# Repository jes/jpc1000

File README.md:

# JPC-1000

This is a repo containing Arduino code, KiCad files for PCBs, and FreeCAD files for the 3d-printed case.

Read more about the project on my blog: https://incoherency.co.uk/blog/stories/process-controller.html

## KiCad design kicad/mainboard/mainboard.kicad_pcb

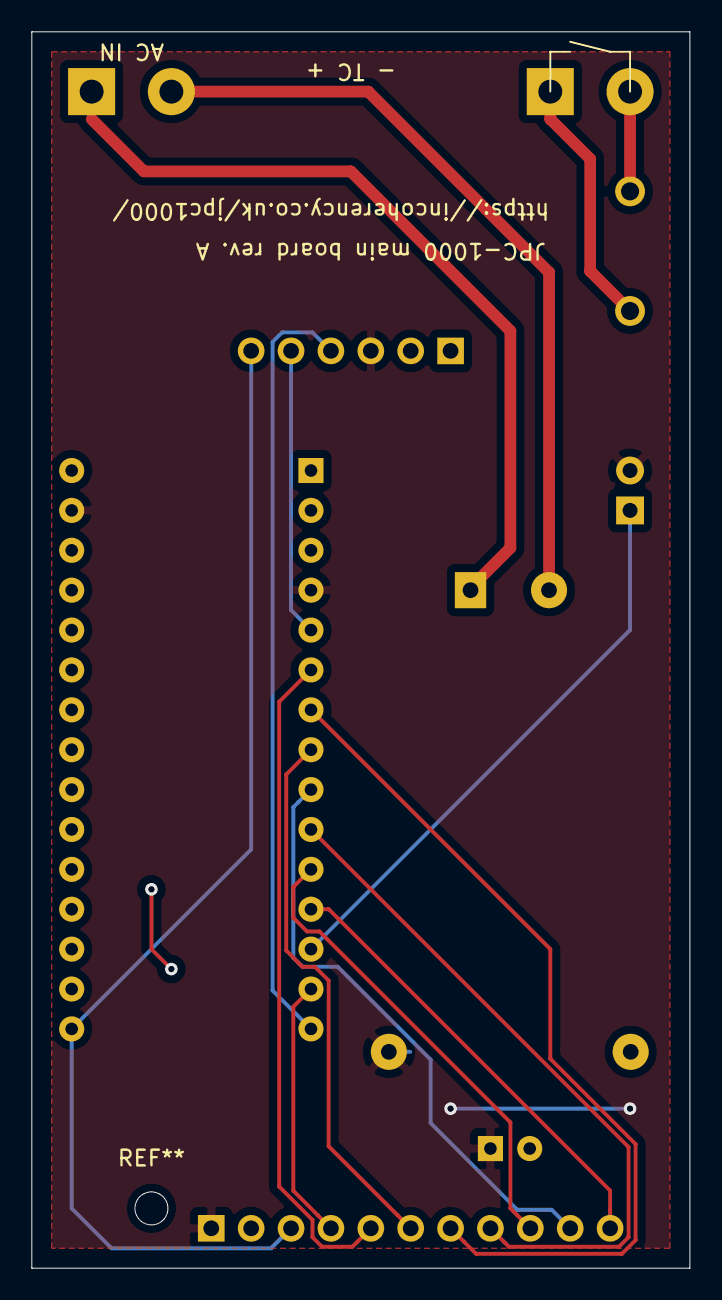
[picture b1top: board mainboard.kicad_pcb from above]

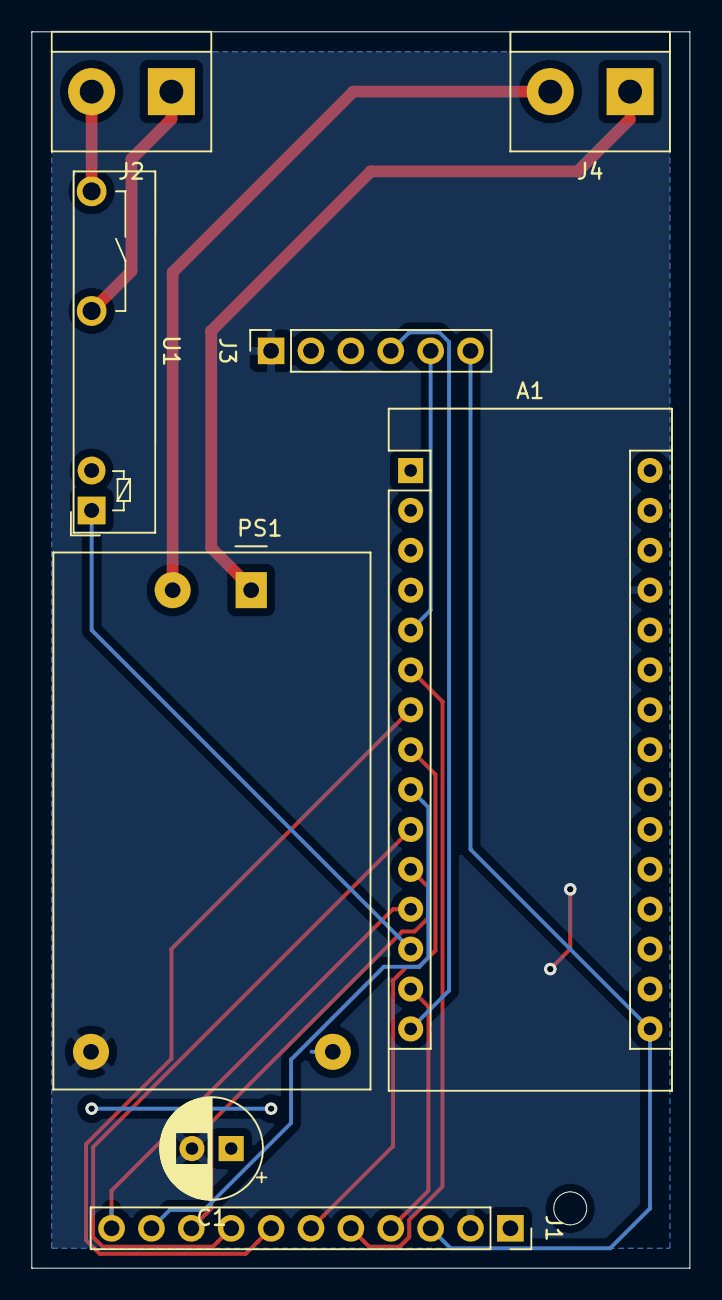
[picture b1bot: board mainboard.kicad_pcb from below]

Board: 2 copper layers, 41.9 x 78.7 mm, 8 parts (8 on the bottom side), 18 nets.

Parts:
A1: Arduino_Nano_v2.x; Arduino_Nano
C1: CP; CP_Radial_D6.3mm_P2.50mm
J1: Conn_01x11_Female; PinSocket_1x11_P2.54mm_Vertical
J2, J4: Screw_Terminal_01x02; TerminalBlock_bornier-2_P5.08mm
J3: Conn_01x06_Female; PinSocket_1x06_P2.54mm_Vertical
PS1: HLK-PM01; Converter_ACDC_HiLink_HLK-PMxx
U1: 34.81-8240; Omron-G3MB-202P

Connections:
unnamed: A1.5, J3.5
unnamed: A1.6, J1.5
unnamed: A1.7, J1.7
unnamed: A1.8, J1.6
unnamed: A1.9, J1.10
unnamed: A1.10, J1.8
unnamed: A1.11, J1.9
unnamed: A1.12, J1.11
unnamed: A1.13, U1.A2
unnamed: A1.14, J1.4
unnamed: A1.15, J3.4
unnamed: A1.16, J1.3, J3.6
unnamed: A1.27, C1.2, J1.2, J3.1, PS1.4
unnamed: A1.4, A1.29, C1.1, J1.1, J3.3, PS1.3, U1.A1
unnamed: J2.1, U1.11
unnamed: J2.2, U1.14
unnamed: J4.1, PS1.1
unnamed: J4.2, PS1.2

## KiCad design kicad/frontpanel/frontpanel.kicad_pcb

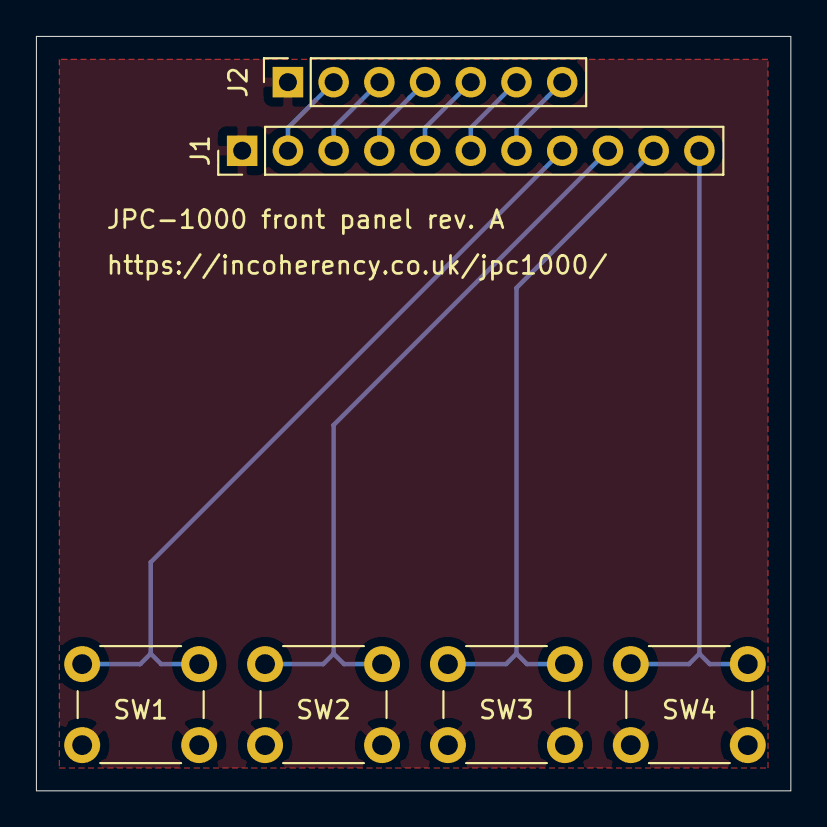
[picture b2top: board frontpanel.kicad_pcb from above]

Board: 2 copper layers, 41.9 x 41.9 mm, 6 parts (0 on the bottom side), 11 nets.

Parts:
J1: Conn_01x11_Male; PinHeader_1x11_P2.54mm_Vertical
J2: Conn_01x07_Female; PinSocket_1x07_P2.54mm_Vertical
SW1, SW2, SW3, SW4: SW_Push; SW_PUSH_6mm_H4.3mm

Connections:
unnamed: J1.1, J2.1, SW1.2, SW2.2, SW3.2, SW4.2
unnamed: J1.2, J2.2
unnamed: J1.3, J2.3
unnamed: J1.4, J2.4
unnamed: J1.5, J2.5
unnamed: J1.6, J2.6
unnamed: J1.7, J2.7
unnamed: J1.8, SW1.1
unnamed: J1.9, SW2.1
unnamed: J1.10, SW3.1
unnamed: J1.11, SW4.1

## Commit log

2019-08-17 Some segment editing ui
2019-08-18 Load/save config in EEPROM
2019-08-18 Draw segment descriptions (apart from duration because we can't format times yet)
2019-08-18 Add 'reset all' option, and switch heater on and off with duty cycle
2019-08-18 Format floats and times, add 'Save' button to segment editing menu
2019-08-18 Format times better, store min_time, use fewer segments because low on memory
2019-08-18 Free up 1% extra memory
2019-08-18 Store manual_control in eeprom; edit in menu
2019-08-18 Initial implementation of number editing
2019-08-18 Edit setpoint
2019-08-18 Key repeat on editnumber screen
2019-08-18 Increase stepsize when button is held down
2019-08-18 Start of time editing, and make the Run button do something
2019-08-18 Bounds-check in editnumber
2019-08-18 Edit all settings
2019-08-19 Set duty cycle manually, fix bugs
2019-08-19 Show Ti and Td as 'off' if 0
2019-08-19 Run program, sort out update logic of main display
2019-08-19 For consistency, ramp first segment from initial setpoint instead of initial temperature
2019-08-19 Fix segment time display
2019-08-19 Don't choke on 0-duration ramp
2019-08-19 More notes, include MAX31855 lib
2019-08-19 Add kicad project
2019-08-19 Add ssr module
2019-08-20 Use MAX31855, fix PID
2019-08-20 Actually fix PID
2019-08-23 Remove segments properly
2019-08-23 Show state even if program is running
2019-08-23 Never switch the heater more often than once per min_time
2019-08-26 Add CAD for case
2019-08-26 Handle errors from the thermocouple reader
2019-08-26 Fix up a couple of errors on the mainboard PCB
2019-09-01 Add README
2019-09-01 Fix URL
2019-09-02 Explicitly set not-safe-to-operate if too long without a good temperature reading
